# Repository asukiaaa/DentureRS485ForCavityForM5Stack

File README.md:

# M5StackCavityDentureRS485

A kicad project for denture for M5StackCavity.

# License

MIT

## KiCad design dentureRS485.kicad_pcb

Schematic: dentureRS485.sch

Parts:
C1: 0.1uf; C_0603_1608Metric
J1: Conn_01x04; PinHeader_1x04_P1.27mm_Vertical
J2: Conn_01x08; PinHeader_1x08_P1.27mm_Vertical
J3: free_holes; Pads_1x30_P1.27mm_Vertical
J4: Conn_01x08; RJ45_Neltron_Industrial_7810-8P8C
J5: Conn_01x02; PinHeader_1x02_P1.27mm_Vertical
JP1, JP2, JP3, JP4, JP5, JP6, JP7: Jumper; SolderJumper-2_P1.3mm_Bridged_RoundedPad1.0x1.5mm
R1: 220; R_0603_1608Metric
U1: SP3485EN; SOIC-8_3.9x4.9mm_P1.27mm

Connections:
+3V3: C1.2, J3.11, U1.8 (VCC)
+5V: J3.27
+BATT: J3.29
/0: J3.23
/1: J3.13
/2: J3.20
/3: J3.14
/5: J3.19, JP2.2, JP3.2
/12: J3.22
/13: J3.21
/15: J3.24
/16: J3.16, JP1.2
/17: J3.15, JP4.2
/18: J3.12
/19: J3.10
/21: J3.18
/22: J3.17
/23: J3.8
/25: J3.7
/26: J3.9
/34: J3.25
/35: J3.1
/36: J3.3
/A+: J5.1, JP6.2, R1.1, U1.6 (A)
/B-: J5.2, JP5.2, R1.2, U1.7 (B)
/HPWR: J3.26, J3.28, J3.30
/RST: J3.5
GND: C1.1, J3.2, J3.4, J3.6, JP7.2, U1.5 (GND)
unnamed: J1.1, JP1.1, U1.1 (RO)
unnamed: J1.2, JP2.1, U1.2 (~RE~)
unnamed: J1.3, JP3.1, U1.3 (DE)
unnamed: J1.4, JP4.1, U1.4 (DI)
unnamed: J2.1, J4.1
unnamed: J2.2, J4.2, JP7.1
unnamed: J2.3, J4.3, JP6.1
unnamed: J2.4, J4.4
unnamed: J2.5, J4.5
unnamed: J2.6, J4.6, JP5.1
unnamed: J2.7, J4.7
unnamed: J2.8, J4.8

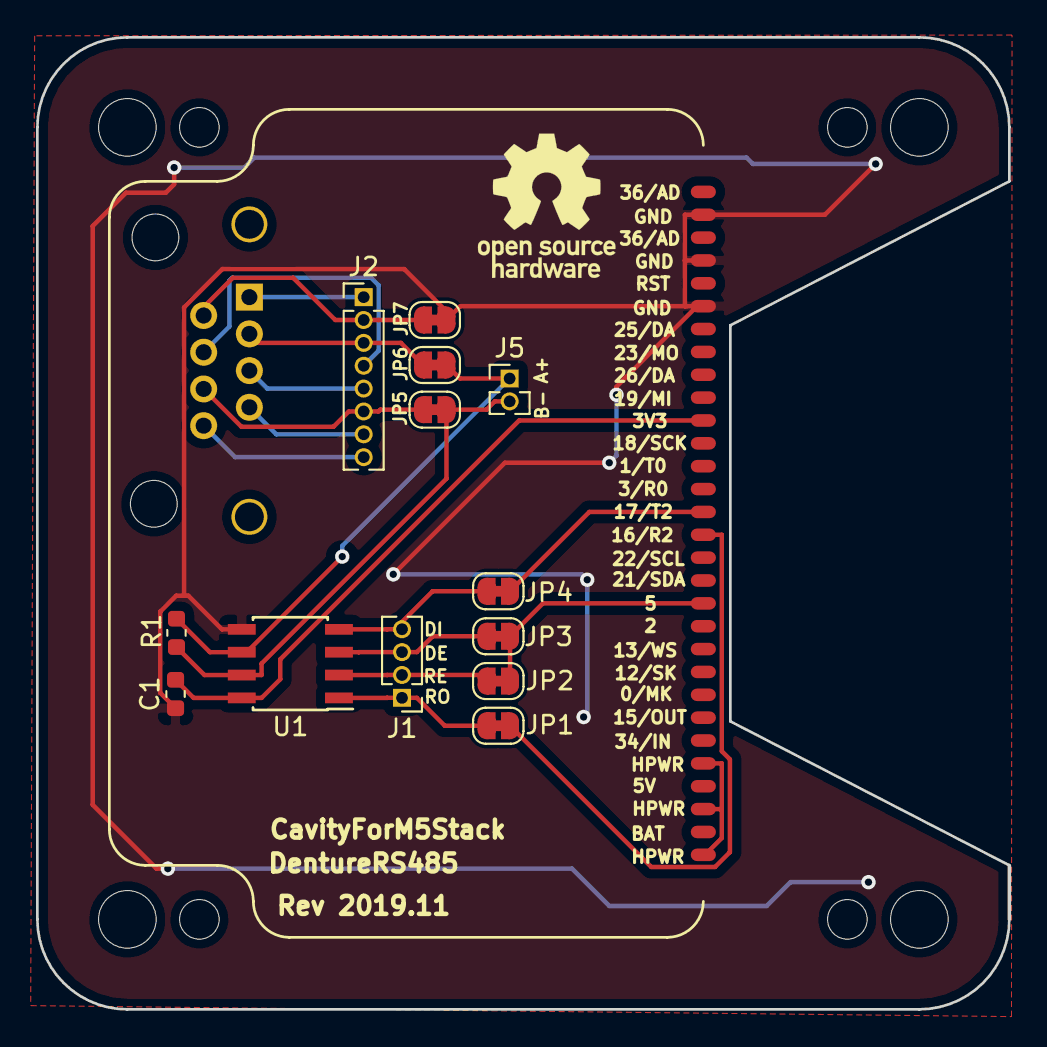
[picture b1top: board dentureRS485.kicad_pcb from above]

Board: 2 copper layers, 54.0 x 54.0 mm, 28 parts (1 on the bottom side), 20 nets.

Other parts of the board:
OSHWREF2: OSHW-Logo_7.5x8mm_SilkScreen
REF1, REF4, REF6, REF9: MountingHole_3.2mm_M3
REF2, REF3, REF7, REF8: MountingHole_2.2mm_M2
corner1, corner2, corner3, corner4: outer_corner

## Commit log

2019-07-16 Update outter line for M5Stack outer line
2019-07-30 Expand radius of outer corners
2019-08-27 Expand mounting hole size for RJ45
2019-08-27 Removoe gerber files from git
2019-11-16 Change position of lan jack on pcb
2019-11-16 Update project to DentureRS485ForCavityForM5Stack
2019-11-17 Add via for GND
2020-10-29 Save RJ45 connector on my-kicad-footprints
2020-12-10 Add schematic
